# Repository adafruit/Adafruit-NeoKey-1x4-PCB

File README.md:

## Adafruit NeoKey 1x4 QT I2C PCB

<a href="http://www.adafruit.com/products/4980"><br/>
Click here to purchase one from the Adafruit shop</a>

PCB files for the Adafruit NeoKey 1x4 QT I2C. 

Format is EagleCAD schematic and board layout
* https://www.adafruit.com/product/4980

### Description

The only thing better than a nice mechanical key is, perhaps, FOUR mechanical keys that also can glow any color of the rainbow - and that's what the Adafruit NeoKey 1x4 QT I2C Breakout will let you do! This longgg 3" x 0.8" PCB fits four Cherry MX or compatible switches and make it easy to use with a breadboard/perfboard or with a STEMMA QT (Qwiic) connector for instant I2C connectivity on any platform.

Please note, each order comes with one assembled and programmed PCB but no switches or keycaps or microcontroller. Most folks have specific key switches and keycaps they want to include, this is just the controller board that plugs into a microcontroller.

The breakout has four Kailh sockets, which means you can plug in any MX-compatible switch instead of soldering it in. You may need a little glue to keep the switch in place: hot glue or a dot of epoxy worked fine for us. Each key also has a reverse-mount NeoPixel pointing up through the spot where many switches would have an LED to shine through.

A microcontroller is pre-programmed with our seesaw firmware so button presses and NeoPixel-controlling is done all over I2C. You can even connect multiple board by chaining the I2C and soldering closed the I2C address jumpers - with four jumpers you can have up to 16 of these boards on a single I2C bus. We have Arduino and CircuitPython/Python libraries for controlling the NeoKey 1x4's so you can use any microcontroller/computer for quick creation of a custom macropad.

You can also fit the breakouts onto a breadboard if you like - with two sets of breakout pads, there's plenty of flexibility for any kind of use. There are two rows of 6-pin contacts on a 0.1" grid on both sides. Solder in both sides for mechanical stability.

Soldering is required to attach the header for breadboard use, you may also need to solder jumpers closed to connect multiple boards together. A microcontroller is required to drive this board, it isn't stand-alone. Keys & keycaps are not included: Use any MX-compatible switch: Kailh, Gateron, etc all work!

### License

Adafruit invests time and resources providing this open source design, please support Adafruit and open-source hardware by purchasing products from [Adafruit](https://www.adafruit.com)!

Designed by Limor Fried/Ladyada for Adafruit Industries.

Creative Commons Attribution/Share-Alike, all text above must be included in any redistribution. 
See license.txt for additional details.

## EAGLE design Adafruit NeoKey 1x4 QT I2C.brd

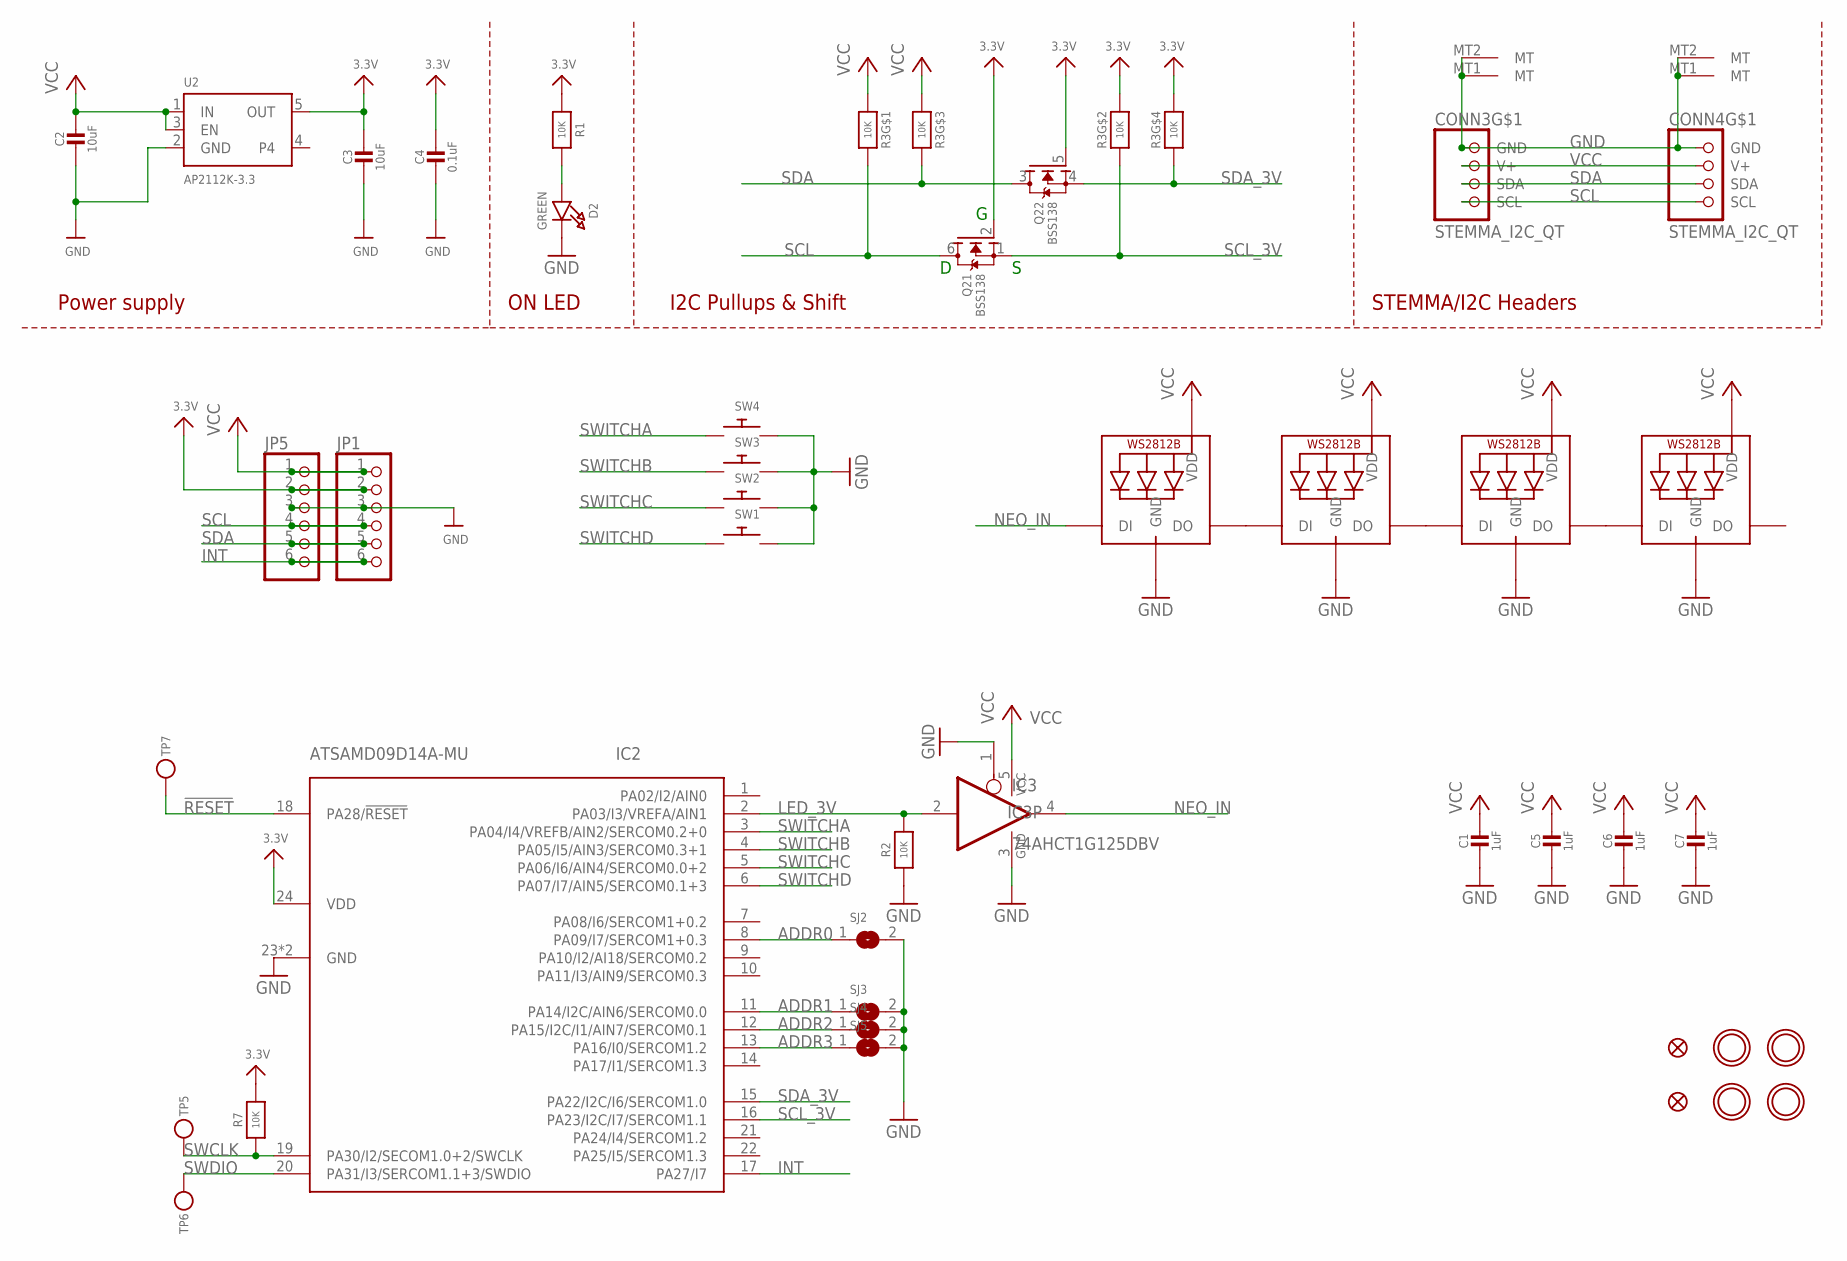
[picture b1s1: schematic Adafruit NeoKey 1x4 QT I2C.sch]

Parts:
C1, C5, C6, C7: 1uF; 0603-NO
C2, C3: 10uF; 0805-NO
C4: 0.1uF; 0603-NO
CONN3, CONN4: STEMMA_I2C_QT; JST_SH4
D2: GREEN; CHIPLED_0603_NOOUTLINE
FID1, FID2: FIDUCIAL_1MM
IC2: ATSAMD09D14A-MU; QFN24_4MM
IC3: 74AHCT1G125DBV; SOT23-5
JP1, JP5: HEADER-1X670MIL; 1X06_ROUND_70
LED1, LED2, LED3, LED4: WS2812B_SK6812E; NEO3535_REVERSE
Q2: BSS138; SOT363
R1, R2, R7: 10K; 0603-NO
R3: 10K; RESPACK_4X0603
SJ2, SJ3, SJ4, SJ5: SOLDERJUMPER; SOLDERJUMPER_ARROW_NOPASTE
SW1, SW2, SW3, SW4: SWITCH_PUSHBUTTON_KAILH_SOCKET; KAILH_SOCKET
TP5, TP6, TP7: TESTPOINTROUND1.5MM; TESTPOINT_ROUND_1.5MM
U2: AP2112K-3.3; SOT23-5
U$3, U$17, U$19, U$21: MOUNTINGHOLE2.5; MOUNTINGHOLE_2.5_PLATED

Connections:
3.3V: C3.1, C4.1, IC2.24 (VDD), JP1.2, JP5.2, Q2.2 (G), Q2.5 (G), R1.1, R3.2 (1), R3.4 (1), R7.2, U2.5 (OUT)
!RESET: IC2.18 (PA28/!RESET), TP7.P$1
ADDR0: IC2.8 (PA09/I7/SERCOM1+0.3), SJ2.1
ADDR1: IC2.11 (PA14/I2C/AIN6/SERCOM0.0), SJ3.1
ADDR2: IC2.12 (PA15/I2C/I1/AIN7/SERCOM0.1), SJ4.1
ADDR3: IC2.13 (PA16/I0/SERCOM1.2), SJ5.1
GND: C1.2, C2.2, C3.2, C4.2, C5.2, C6.2, C7.2, CONN3.1 (GND), CONN3.MT1 (MT), CONN3.MT2 (MT), CONN4.1 (GND), CONN4.MT1 (MT), CONN4.MT2 (MT), D2.C, IC2.23 (GND), IC2.THERM (GND), IC3.1 (OE), IC3.3 (GND), JP1.3, JP5.3, LED1.3-GND (GND), LED2.3-GND (GND), LED3.3-GND (GND), LED4.3-GND (GND), R2.1, SJ2.2, SJ3.2, SJ4.2, SJ5.2, SW1.1, SW2.1, SW3.1, SW4.1, U2.2 (GND)
INT: IC2.17 (PA27/I7), JP1.6, JP5.6
LED_3V: IC2.2 (PA03/I3/VREFA/AIN1), IC3.2 (I), R2.2
unnamed: D2.A, R1.2
unnamed: LED1.2-DOUT (DO), LED2.4-DIN (DI)
unnamed: LED2.2-DOUT (DO), LED3.4-DIN (DI)
unnamed: LED3.2-DOUT (DO), LED4.4-DIN (DI)
NEO_IN: IC3.4 (O), LED1.4-DIN (DI)
SCL: CONN3.4 (SCL), CONN4.4 (SCL), JP1.4, JP5.4, Q2.6 (D), R3.8 (2)
SCL_3V: IC2.16 (PA23/I2C/I7/SERCOM1.1), Q2.1 (S), R3.7 (2)
SDA: CONN3.3 (SDA), CONN4.3 (SDA), JP1.5, JP5.5, Q2.3 (D), R3.6 (2)
SDA_3V: IC2.15 (PA22/I2C/I6/SERCOM1.0), Q2.4 (S), R3.5 (2)
SWCLK: IC2.19 (PA30/I2/SECOM1.0+2/SWCLK), R7.1, TP5.P$1
SWDIO: IC2.20 (PA31/I3/SERCOM1.1+3/SWDIO), TP6.P$1
SWITCHA: IC2.3 (PA04/I4/VREFB/AIN2/SERCOM0.2+0), SW4.2
SWITCHB: IC2.4 (PA05/I5/AIN3/SERCOM0.3+1), SW3.2
SWITCHC: IC2.5 (PA06/I6/AIN4/SERCOM0.0+2), SW2.2
SWITCHD: IC2.6 (PA07/I7/AIN5/SERCOM0.1+3), SW1.2
VCC: C1.1, C2.1, C5.1, C6.1, C7.1, CONN3.2 (V+), CONN4.2 (V+), IC3.5 (VCC), JP1.1, JP5.1, LED1.1-VDD (VDD), LED2.1-VDD (VDD), LED3.1-VDD (VDD), LED4.1-VDD (VDD), R3.1, R3.3 (1), U2.1 (IN), U2.3 (EN)

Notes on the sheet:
I2C Pullups & Shift
STEMMA/I2C Headers
ON LED
Power supply

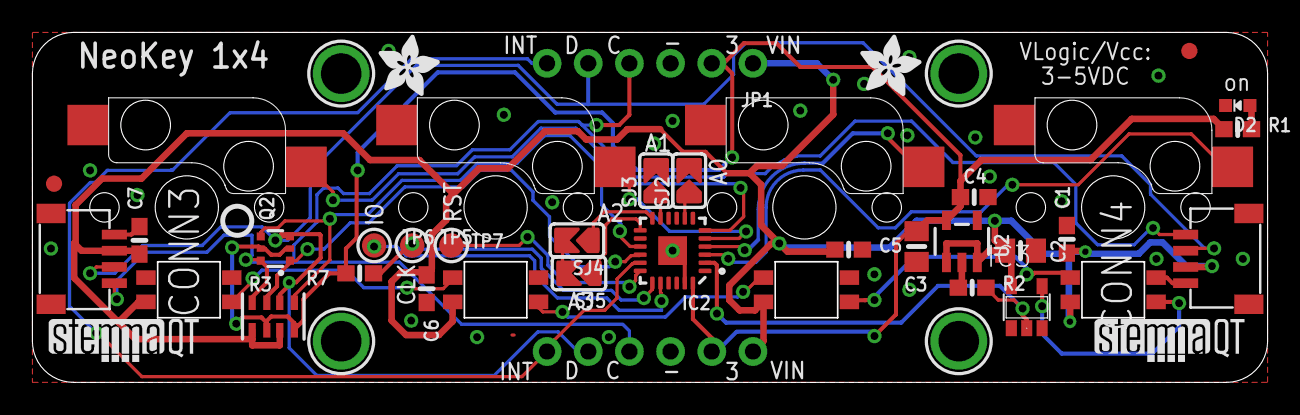
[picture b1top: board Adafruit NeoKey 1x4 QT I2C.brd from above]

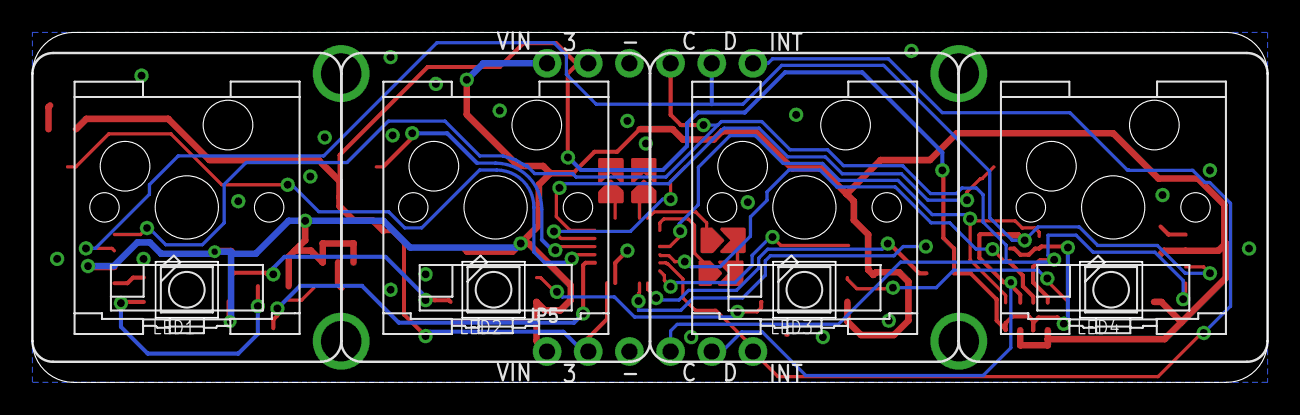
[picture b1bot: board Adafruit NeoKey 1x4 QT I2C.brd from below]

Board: 2 copper layers, 76.1 x 21.5 mm, 46 parts (9 on the bottom side), 25 nets.

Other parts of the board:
U$2, U$9: ADAFRUIT_3.5MM
U$25: PCBFEAT-REV-040
U$30, U$31: STEMMAQT

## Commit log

2021-06-25 Adding board files.

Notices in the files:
parts and their libraries:
microbuilder: This work is placed in the public domain, and may be freely used for commercial and non-commercial work with the following conditions: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
